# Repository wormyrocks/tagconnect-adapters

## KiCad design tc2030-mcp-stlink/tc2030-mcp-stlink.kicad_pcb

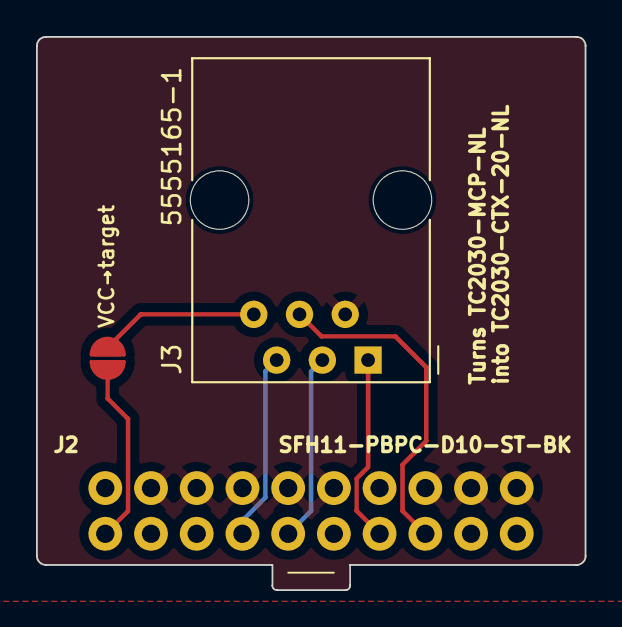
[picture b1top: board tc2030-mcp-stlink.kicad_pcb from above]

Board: 2 copper layers, 30.5 x 30.7 mm, 3 parts (0 on the bottom side), 7 nets.

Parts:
J2: SFH11-PBPC-D10-ST-BK; CONN_2X10_100MIL
J3: 5555165-1; CONN_RJ12
JP1: JUMPER_SOLDER_1MM

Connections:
GND: J2.4 (GND), J2.6 (GND), J2.8 (GND), J2.10 (GND), J2.12 (GND), J2.14 (GND), J2.16 (GND), J2.18 (GND), J2.20 (GND), J3.2
NRST: J2.15 (~SRST), J3.4
unnamed: J2.1 (VTREF), JP1.2
SWCLK: J2.9 (TCK/SWDCLK), J3.3
SWDIO: J2.7 (TMS/SWDIO), J3.5
SWO: J2.13 (TDO/SWO), J3.1
VCC: J3.6, JP1.1

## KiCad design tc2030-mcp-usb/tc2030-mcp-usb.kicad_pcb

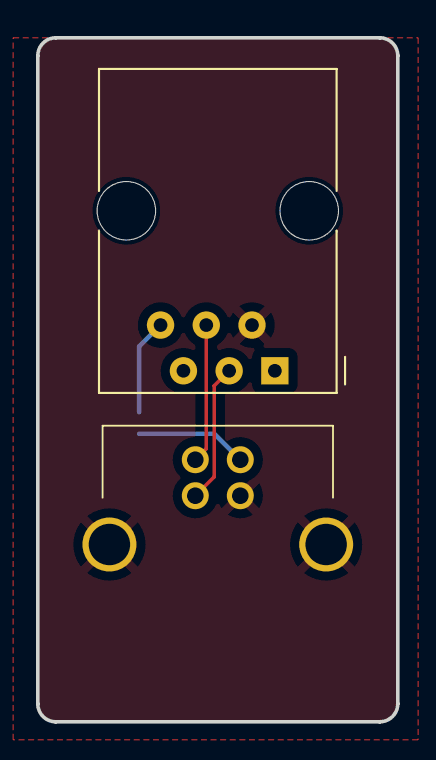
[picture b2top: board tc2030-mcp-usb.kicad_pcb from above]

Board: 2 copper layers, 20.0 x 38.0 mm, 3 parts (1 on the bottom side), 5 nets.

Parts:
J2: CONN_USB; CONN_USB_B_USB-B1HSB6
J3: CONN_6; CONN_RJ12
JP1: JUMPER_SOLDER_1MM

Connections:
GND: J2.4 (GND), J2.CASE, J3.2
unnamed: J2.1 (VBUS), JP1.1
USB_D+: J2.3 (D+), J3.3
USB_D-: J2.2 (D-), J3.4
VBUS: J3.6, JP1.2

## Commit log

2023-09-28 add kicad files, remove references to biolite before making repo public
2023-10-02 add altera adapter
2023-10-25 flipped st-link pinout
2023-11-16 fix stlink pinout
